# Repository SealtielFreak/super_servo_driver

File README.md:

# Super Servo Board
Smart Servo Board for SG-90 and MG-996/995

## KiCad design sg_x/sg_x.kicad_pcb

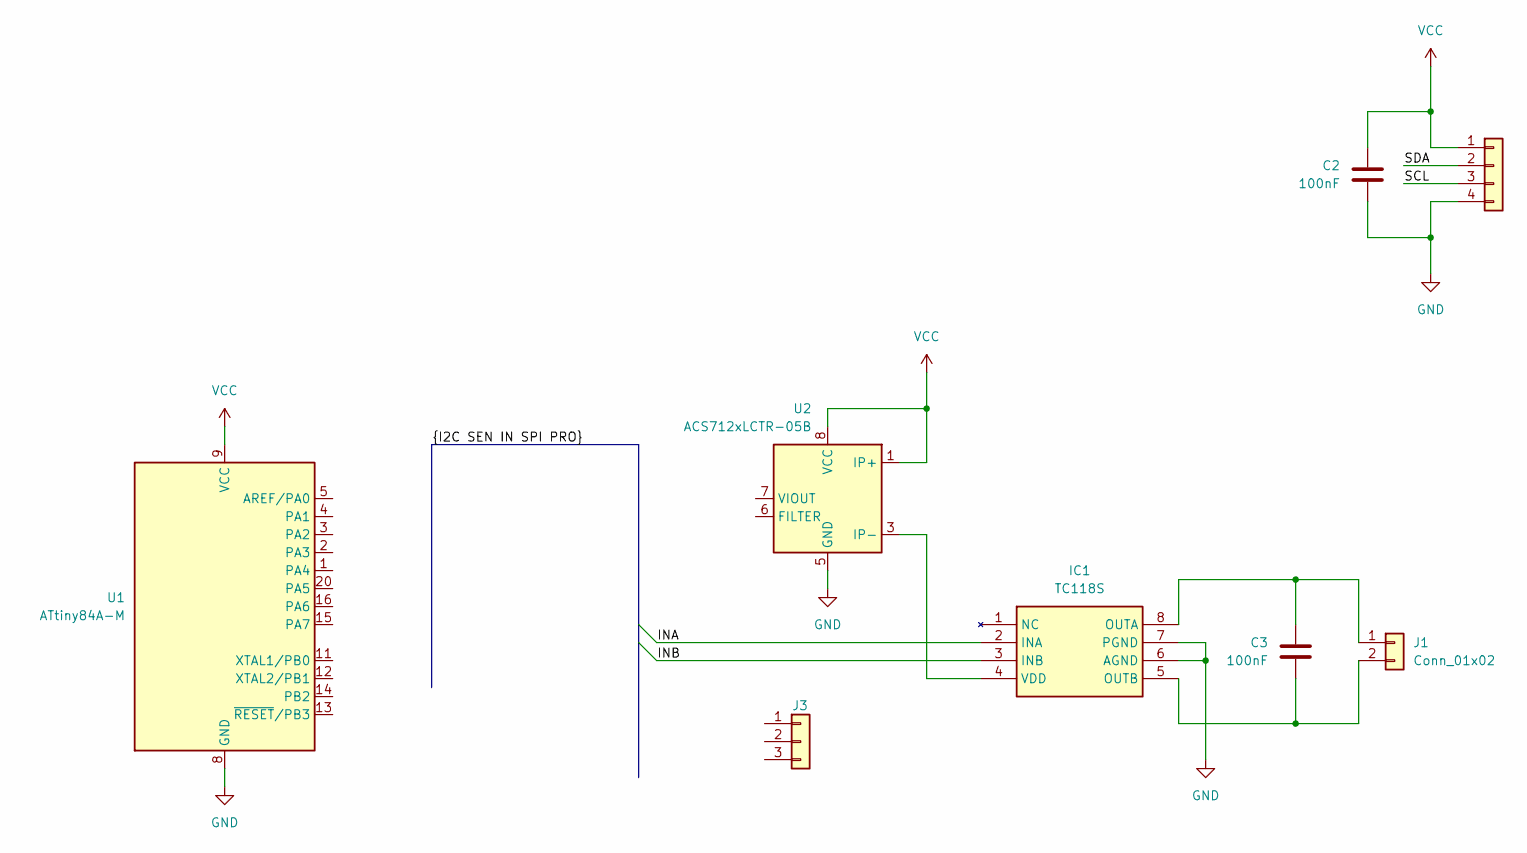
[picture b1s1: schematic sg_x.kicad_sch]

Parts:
C2, C3: 100nF; C_0603_1608Metric
IC1: TC118S; SOIC-8_3.9x4.9mm_P1.27mm; Manufacturer_Part_Number TC118S
J1: Conn_01x02; Connector_DC_Motor
J2: Conn_01x04; Connector_Servo_Driver_SMD
J3: Conn_01x03; Connector_Servo_Driver_ADC
U1: ATtiny84A-M; QFN-20-1EP_4x4mm_P0.5mm_EP2.6x2.6mm
U2: ACS712xLCTR-05B; SOIC-8_3.9x4.9mm_P1.27mm

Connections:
/INA: IC1.2 (INA)
/INB: IC1.3 (INB)
/SCL: J2.3
/SDA: J2.2
GND: C2.2, IC1.6 (AGND), IC1.7 (PGND), J2.4, U1.8 (GND), U1.21 (GND), U2.5 (GND)
unnamed: C3.1, IC1.8 (OUTA), J1.1
unnamed: C3.2, IC1.5 (OUTB), J1.2
unnamed: IC1.4 (VDD), U2.3 (IP-), U2.4 (IP-)
VCC: C2.1, J2.1, U1.9 (VCC), U2.1 (IP+), U2.2 (IP+), U2.8 (VCC)

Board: 2 copper layers, 8 parts (4 on the bottom side), 5 nets, no tracks yet.

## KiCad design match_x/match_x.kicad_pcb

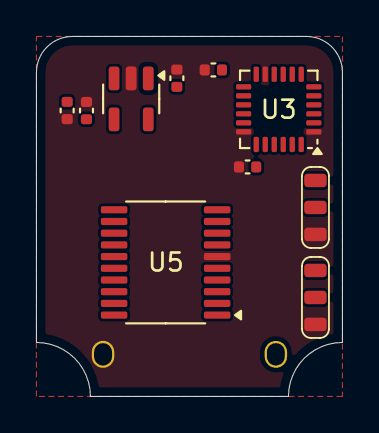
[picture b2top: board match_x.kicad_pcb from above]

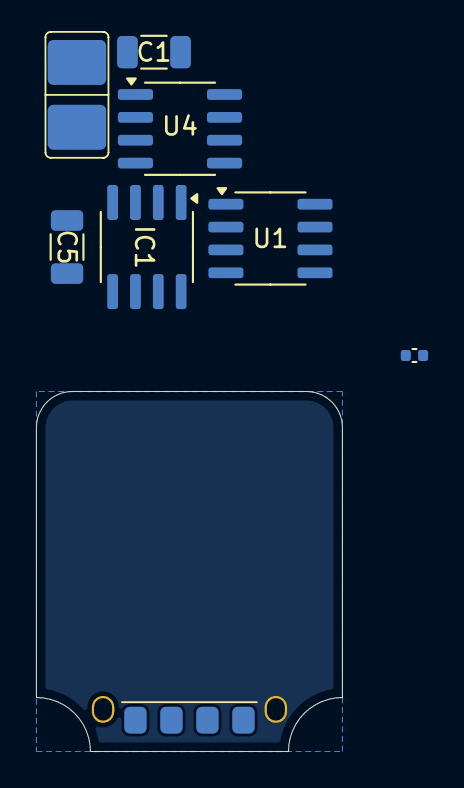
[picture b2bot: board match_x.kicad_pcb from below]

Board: 2 copper layers, 17.0 x 20.0 mm, 18 parts (8 on the bottom side), 22 nets, no tracks yet.

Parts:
C1: 1nF; C_1206_3216Metric
C2, C3: 1uF; C_0402_1005Metric
C4, C6, C7: 100nF; C_0402_1005Metric
C5: 104pF; C_1206_3216Metric
C8: 220pF; C_0402_1005Metric
IC1: TC118S; SOIC-8_3.9x4.9mm_P1.27mm
J1: Conn_01x02; Connector_Motor_DC
J2, J3: Conn_01x03; Connector_Sensor_Signal
J4: Conn_01x06; Connector_User_Interface
U1: X9C104P; SOIC-8_3.9x4.9mm_P1.27mm
U2: LD3985G18R_TSOT23; TSOT-23-5
U3: MPU-6050; InvenSense_QFN-24_4x4mm_P0.5mm
U4: ACS712xLCTR-05B; SOIC-8_3.9x4.9mm_P1.27mm
U5: ATtiny861A-X; TSSOP-20_4.4x6.5mm_P0.65mm

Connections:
+3.3V: C3.1, J2.1, J3.1, U2.5 (VOUT), U3.8 (VLOGIC), U3.13 (VDD), U4.8 (VCC), U5.5 (VCC)
/ASEN: U4.7 (VIOUT), U5.7 (XTAL1/PB4)
/BSEN: J2.2, U5.9 (PB6)
/CS: J4.5, U5.14 (PA4)
/CSEN: J3.2, U5.8 (XTAL2/PB5)
/INA: IC1.2 (INA), U5.3 (PB2)
/INB: IC1.3 (INB), U5.4 (PB3)
/MISO: J4.3, U5.18 (PA2)
/MOSI: J4.2, U5.19 (PA1)
/SCK: J4.4, U5.17 (AREF/PA3)
/SCL: U3.23 (SCL), U5.1 (PB0)
/SDA: U3.24 (SDA), U5.2 (PB1)
GND: C1.2, C2.2, C3.2, C4.2, C6.2, C7.2, C8.2, IC1.6 (AGND), IC1.7 (PGND), J2.3, J3.3, J4.6, U2.2 (GND), U3.1 (CLKIN), U3.11 (FSYNC), U3.18 (GND), U4.5 (GND), U5.6 (GND)
unnamed: C5.1, IC1.8 (OUTA), J1.1
unnamed: C5.2, IC1.5 (OUTB), J1.2
unnamed: IC1.4 (VDD), U4.3 (IP-), U4.4 (IP-)
unnamed: C4.1, U2.4 (BYP)
unnamed: C6.1, U2.3 (INH)
unnamed: C8.1, U3.20 (CPOUT)
unnamed: C7.1, U3.10 (REGOUT)
unnamed: C1.1, U4.6 (FILTER)
VCC: C2.1, J4.1, U2.1 (VIN), U4.1 (IP+), U4.2 (IP+)

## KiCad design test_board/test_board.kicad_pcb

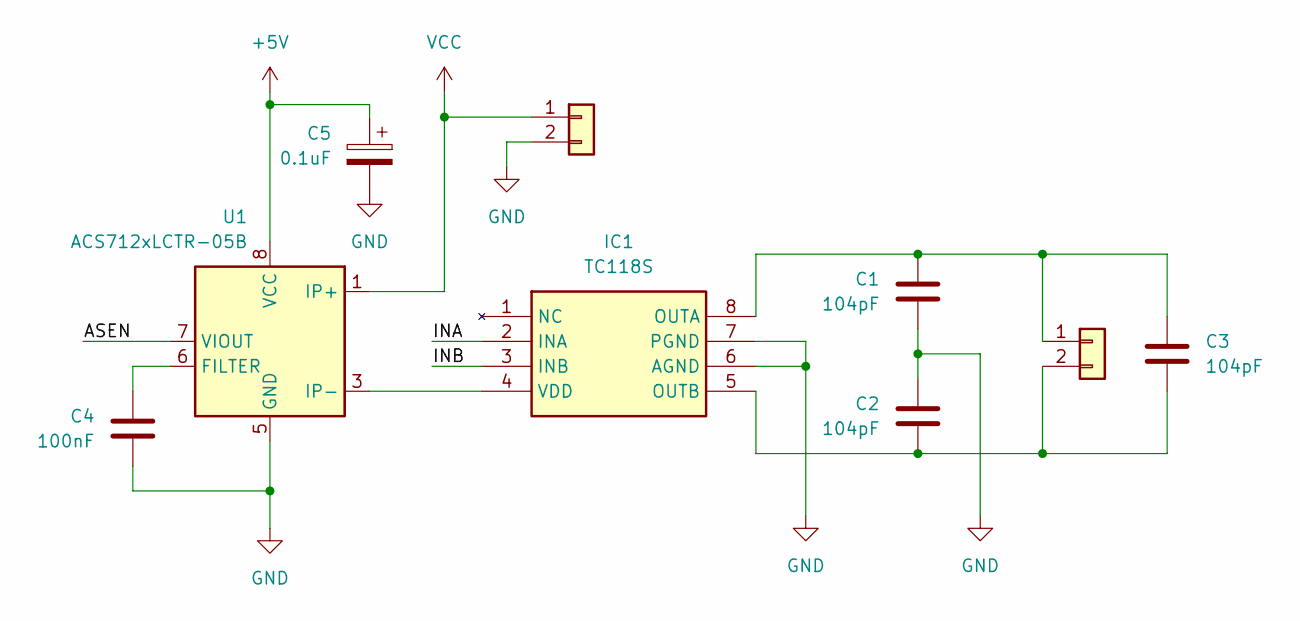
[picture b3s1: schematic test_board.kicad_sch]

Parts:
C1, C2, C3: 104pF; C_Disc_D3.0mm_W2.0mm_P2.50mm
C4: 100nF; C_Disc_D3.0mm_W2.0mm_P2.50mm
C5: 0.1uF; CP_Radial_D4.0mm_P1.50mm
IC1: TC118S; SOIC127P600X155-8N; Manufacturer_Part_Number TC118S
J1: MotorConnection; TerminalBlock_bornier-2_P5.08mm
J3: PowerSupply; TerminalBlock_bornier-2_P5.08mm
U1: ACS712xLCTR-05B; SOIC-8_3.9x4.9mm_P1.27mm

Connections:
+5V: C5.1, U1.8 (VCC)
/ASEN: U1.7 (VIOUT)
/INA: IC1.2 (INA)
/INB: IC1.3 (INB)
GND: C1.2, C2.1, C4.2, C5.2, IC1.6 (AGND), IC1.7 (PGND), J3.2, U1.5 (GND)
unnamed: C1.1, C3.1, IC1.8 (OUTA), J1.1
unnamed: C2.2, C3.2, IC1.5 (OUTB), J1.2
unnamed: IC1.4 (VDD), U1.3 (IP-), U1.4 (IP-)
unnamed: C4.1, U1.6 (FILTER)
VCC: J3.1, U1.1 (IP+), U1.2 (IP+)

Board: 2 copper layers, 9 parts (0 on the bottom side), 7 nets, no tracks yet.

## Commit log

2024-05-05 Minor changes
2024-05-05 Add MG-X
2024-05-09 Testing board
2024-05-09 Improved MG-X
2024-05-09 Create footprint connector
2024-05-09 Minor changes in PCB
2024-05-09 Change LICENSE
2024-05-09 Improved PCB
2024-05-09 Match-X Controller is create
2024-05-10 Potenciometer installed
2024-05-10 Ceate model simulator
2024-05-10 README written
2024-05-10 Update .gitignore for work with Proteus
2024-05-10 Improved model simulator
2024-05-13 Commit the SG-X improved
2024-05-22 Minor changes (Resize for HAL sensor)
2024-05-22 Second commit of Proteus model simulator
2024-05-22 First commit of driver controller system in C/C++
